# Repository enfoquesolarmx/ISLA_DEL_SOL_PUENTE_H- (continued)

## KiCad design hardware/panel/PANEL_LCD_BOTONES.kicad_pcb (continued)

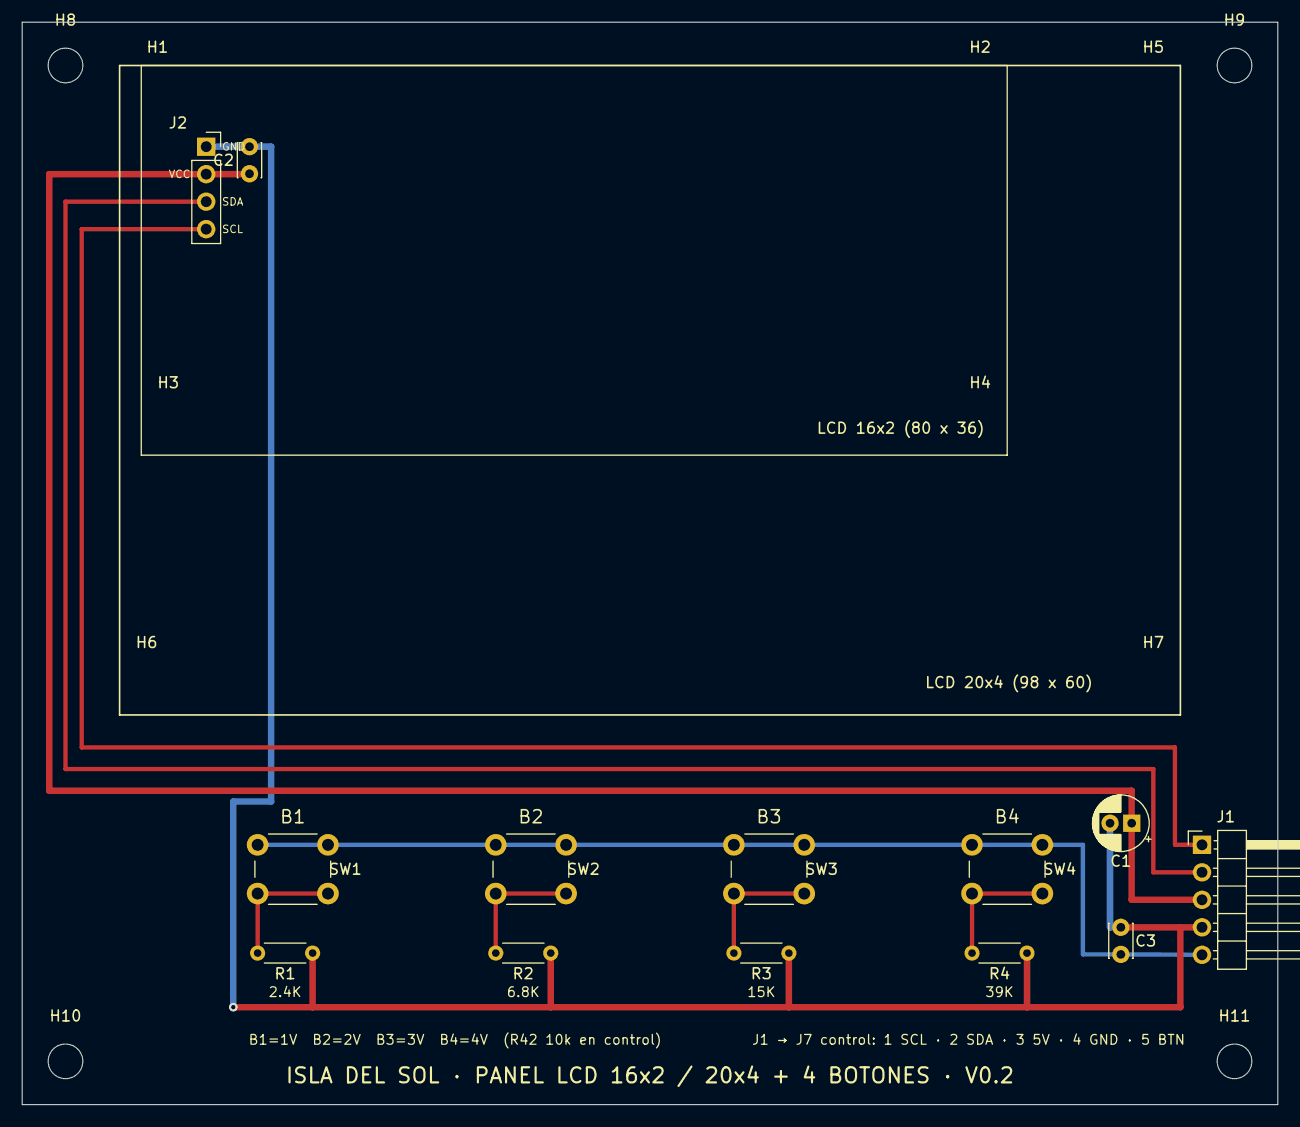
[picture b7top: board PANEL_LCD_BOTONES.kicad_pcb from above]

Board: 2 copper layers, 116.0 x 100.0 mm, 24 parts (0 on the bottom side), 9 nets.

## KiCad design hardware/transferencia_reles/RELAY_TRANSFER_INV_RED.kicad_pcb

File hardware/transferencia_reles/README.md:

# Tarjeta de transferencia de carga V0.1: 5 relés (red · inversor · cargador)

Tarjeta de potencia de 127 V que decide **de dónde se alimenta la casa**: de la **red** o del **inversor**. También conecta el **transformador a la red para cargar la batería** y hace la **unión neutro–tierra (N–PE)** cuando el inversor es la fuente principal.

Recibe tres órdenes de la tarjeta de control por un cable plano IDC de 8 hilos (J15) y no tiene microcontrolador propio. **Si se va la energía de 15 V, se suelta el cable o el microcontrolador de la tarjeta de control está en reset, todos los relés se sueltan y la casa queda en la red** (falla segura).

> ⚠️ **127 V AC en bornes, pistas y contactos de relé: pueden ser mortales.** Prototipo en desarrollo, no certificado. La decisión de diseño completa está en [DC-019](../../docs/decisiones_criticas.md) y el estudio de referencia industrial en [OutBack FX](../../docs/referencia_outback_fx.md).

*Render 3D de KiCad 9, V0.1. Arriba, la lógica de 15 V (J15, ULN2003A, Q1/Q2) y el título; abajo, los 5 relés, los bornes de 127 V y los capacitores X2/Y2. El modelo de los relés es aproximado (`3d/`).*

---

## 0. Por qué la Isla del Sol necesita esta tarjeta

La Isla del Sol es **inversor y cargador a la vez**: el mismo puente H y el **mismo transformador** sacan 127 V de la batería cuando no hay red, y la cargan desde la **red eléctrica pública** (o un generador) cuando sí hay. Ese doble papel deja tres preguntas que el puente H no puede contestar por sí solo y que esta tarjeta resuelve **con hardware**:

**1. ¿De dónde se alimenta la casa, y cómo se garantiza que nunca sea de las dos fuentes a la vez?**
Si la salida del inversor queda en paralelo con la red, aunque sea un instante:
- la red eléctrica alimenta de reversa al transformador y al puente H y lo destruye (son dos fuentes de 127 V que no están sincronizadas);
- con la red caída, el inversor **energiza la acometida**: 127 V en las líneas de la red eléctrica, donde puede haber un liniero trabajando.

Por eso la transferencia la hace un **conmutador de 2 polos y 2 tiros** (K4 + K2): el mismo contacto que conecta la casa a una fuente la desconecta de la otra. **Ni siquiera un relé soldado forma el paralelo** (análisis de falla en [DC-019](../../docs/decisiones_criticas.md)). Es el principio del equipo de transferencia de los sistemas de respaldo (NOM-001-SEDE-2012 de México, art. 702; equivalente al artículo 702 del NEC de EE. UU.).

**2. ¿Cómo se conecta el transformador a la red para cargar la batería, sin que la casa se quede sin luz?**
En modo cargador, K1 + K3 conectan el transformador al **nodo de la casa**, que sigue en la red por los contactos NC. La casa nunca se queda sin luz mientras se carga, y el candado Q1 impide que "cargar" e "invertir" se pidan al mismo tiempo.

**3. ¿Quién hace la unión neutro–tierra cuando el inversor alimenta la casa?**
Al conmutar también el neutro, el inversor se vuelve un **sistema derivado separadamente**. Necesita su propia unión N–PE (NOM-001-SEDE-2012, 250-30; NEC 250.30), pero **solo** cuando es la fuente: con la red, la unión es la de la acometida, y una segunda unión haría circular corriente por la tierra. K5 la hace de forma automática según el modo del SETUP (sección 4.1). El OutBack FX, la referencia industrial, deja esa decisión al instalador ([estudio](../../docs/referencia_outback_fx.md)).

**Y además, por diseño de la Isla del Sol:**
- **Los 127 V fuera de la tarjeta de control** ([DC-015](../../docs/decisiones_criticas.md)). El microcontrolador, el LCD y los botones solo ven 15 V y un cable plano. Toda la parte de 127 V vive aquí, con 5 mm de separación y ranuras de aislamiento.
- **Falla segura:** sin 15 V, con el cable suelto o con el microcontrolador en reset, la casa queda **en la red**. Si el inversor se apaga por cualquier causa, la casa no se queda a oscuras si hay red.
- **Reparable en la trinchera:** relés de 30 A tipo T90, ULN2003, BC547, 1N4148 y resistencias de agujero pasado. Todo se consigue en una tienda de electrónica local, se cambia con un cautín y está documentado pieza por pieza.

**Dónde se usa:**

| Instalación | Modo normal | Qué hace la tarjeta |
| --- | --- | --- |
| Casa con red inestable (respaldo) | Red | Al fallar la red pasa a inversor (modo CARGA/UPS o CASA); al volver, regresa a la red y carga la batería |
| Sitio aislado con generador | Inversor (CASA) | El generador entra como "red" para cargar la batería y alimentar la casa mientras tanto |
| Solar como fuente principal, red de respaldo | Inversor (CASA) | Usa primero el sol y la batería; la red solo para cargar o cuando la batería se agota |

## 1. Características

| Parámetro | Valor |
| --- | --- |
| Voltaje | 127 V AC / 60 Hz (fase, neutro y tierra física) |
| Corriente de diseño | **10 A RMS continuos** (1270 VA) |
| Relés | 5 × SPDT de 30 A NO / 20 A NC, familia T90. **Bobina de 15 V** (p. ej. Picker PTRH-1C-15S) o Rayex L90S de 12 V con 39 Ω (sección 12) |
| Conmuta | **Fase y neutro** (los dos polos), en transferencia y en cargador |
| Mando | ULN2003A desde 15 V; 3 canales: INV, CARG, TN |
| Candados por hardware | Q1: el inversor bloquea al cargador · Q2: la unión N–PE solo con inversor activo |
| Filtro | C_F 4.7 µF X2 del lado del transformador · CX_RED 0.1 µF X2 + CY_RED 0.1 µF Y2 del lado de la red |
| Versión | **V0.1** (2026-11). En la serigrafía: "ISLA DEL SOL · TARJETA DE TRANSFERENCIA DE CARGA · V0.1.J.G · 2026-11" |
| Placa | 158.4 × 131.1 mm, 2 capas, **1 oz**, 4 barrenos de montaje Ø4.3 mm, **4 ranuras de aislamiento** |
| Separaciones | **≥ 5 mm** de 127 V a lógica · **≥ 3 mm** entre redes de 127 V (verificado con script, secciones 9 y 10) |

## 2. Archivos

| Archivo | Qué es |
| --- | --- |
| `RELAY_TRANSFER_INV_RED.kicad_pro` | Proyecto de KiCad 9 (incluye las exclusiones del DRC: serigrafía sobre las ranuras y las 3 islas unidas por cable) |
| `RELAY_TRANSFER_INV_RED.kicad_sch` | Esquemático, en 5 bloques sobre A3 |
| `RELAY_TRANSFER_INV_RED.kicad_pcb` | Layout |
| `RELAY_TRANSFER_INV_RED.kicad_dru` | **Reglas de separación** de 5 mm y 3 mm para el DRC de KiCad (sección 10). Va en la misma carpeta que el proyecto |
| `auditoria/` | Auditoría térmica a 10 A: script, mapas e informe ([README](auditoria/README.md)) |
| `3d/` | **Modelo 3D aproximado del relé** (`Relay_SPDT_RAYEX-L90S_aprox.step`) y el script que lo genera (CadQuery). KiCad no trae el modelo oficial de esta huella; los relés lo usan con la ruta `${KIPRJMOD}/3d/...` |
| `img/` | Imágenes de este documento |

---

## 3. Cómo funciona

### 3.1 Los relés

Hay dos pares de relés iguales, uno para la **fase (L)** y otro para el **neutro (N)**, más el relé de la unión N–PE.

| Relé | Polo | Función | COM (11) | NC (12), en reposo | NO (14), energizado |
| --- | --- | --- | --- | --- | --- |
| **K4** (K_L2) | L | Transferencia | L-LOAD (casa) | **L-GRID** (red) | L-INV (transformador) |
| **K2** | N | Transferencia | N-LOAD | **N-GRID** | N-INV |
| **K1** (K_L3) | L | Cargador | L-INV | sin conectar | L-LOAD |
| **K3** | N | Cargador | N-INV | sin conectar | N-LOAD |
| **K5** (RL_TN) | N–PE | Unión neutro–tierra | N-INV | sin conectar | TIERRA |

K4 y K2 forman un **conmutador de 2 polos y 2 tiros**: la casa nunca puede tener la red y el inversor al mismo tiempo, porque es el mismo contacto el que cambia de lado.

### 3.2 Los tres canales y los modos

| Canal (salida del ULN2003) | Orden en J15 | Bobinas | LED |
| --- | --- | --- | --- |
| **INV** (AISLAR RED), salida 16 | J15-3 | K4 + K2 | D8 |
| **CARG** (TRAFO), salida 15 | J15-5 | K1 + K3 | D6 |
| **TN**, salida 14 | J15-7, **pasando por Q2** | K5 | D9 |

| Modo | INV | CARG | TN | La casa queda en | El transformador |
| --- | --- | --- | --- | --- | --- |
| **Red** (también: sin 15 V, cable suelto, microcontrolador en reset) | 0 | 0 | 0 | Red | Aislado |
| **Inversor CASA** (fuente principal) | 1 | 0 | 1 | Inversor, **con unión N–PE** (K5) | Alimenta la casa |
| **Inversor CARGA** (UPS de cargas críticas) | 1 | 0 | 0 | Inversor, **sin unión N–PE** | Alimenta las cargas |
| **Cargador** | 0 | 1 | 0 | Red | Conectado a la red por el nodo de la casa |

INV y CARG al mismo tiempo **no existe**: Q1 lo impide (sección 4).

---

## 4. Candados por hardware

*Vista previa aproximada del esquemático, dibujada desde el `.kicad_sch`. Bloques: A · entrada J15, B · candados, C · ULN2003 y LED de 15 V, D · relés, E · potencia de 127 V.*

| Candado | Cómo | Qué evita |
| --- | --- | --- |
| **Pulldowns de 10 kΩ + 10 nF** en INV_CMD, CARG_CMD y TN_OK (R7, R9, R8 y C3, C5, C4) | Con la entrada al aire, el ULN2003 queda apagado | Cable suelto, microcontrolador en reset o pin flotante → la casa queda en la red |
| **Q1** (BC547): base desde INV_CMD por R5 (10 kΩ); colector en CARG_CMD; emisor a GND | Si llega INV, Q1 jala CARG_CMD a 0 V. R11 (1 kΩ) limita la corriente si el microcontrolador manda CARG al mismo tiempo | Inversor y cargador a la vez: el transformador en paralelo con la red mientras alimenta la casa |
| **Q2** (BC547) en seguidor de emisor: colector ← TN_CMD por R13 (1 kΩ); base ← INV_CMD por R14 (10 kΩ); emisor → TN_OK | TN solo llega al ULN si INV también está activo (compuerta AND) | Una **doble unión N–PE** con la de la acometida de la red eléctrica: en modo red o cargador, K2 todavía une N-LOAD con N-GRID |
| **Entradas 4–7 del ULN2003 a GND** | Canales sin uso apagados | Ruido que encienda una salida libre |

Todas las órdenes entran por **1 kΩ en serie** (R10, R11, R13) para proteger los pines del microcontrolador si el cable se pela contra 15 V.

### ⚠️ Q2 hace dos trabajos, no uno — no lo quite

Desde **DC-023** (21 de noviembre de 2026), `TN_CMD` sale del **D13** del CRÍTICO, no del D6. D6 se liberó para `AIN0`, la entrada del comparador analógico, que está cableada en silicio y no se puede mover.

**Y D13 es el pin del LED del Nano, que el bootloader parpadea en cada arranque y en cada reset.** Sin protección, eso serían pulsos al relé K5 de unión N–PE en cada reinicio.

**Q2 es lo que lo vuelve inofensivo:**

```
  reset -> todos los pines del CRITICO en alta impedancia
        -> INV_CMD sin manejar  ->  base de Q2 sin excitar
        -> el bootloader parpadea D13 (TN_CMD)
        -> colector con senal, base sin ella  ->  TN_OK se queda BAJO
```

El orden lo garantiza: **el bootloader corre antes que la aplicación**, así que `INV_CMD` todavía no existe cuando D13 parpadea. Lo mismo vale para la programación por ICSP, donde D13 es **SCK** y conmuta a la frecuencia del programador.

> Q2 ya no es sólo el candado contra la doble unión N–PE: **también es lo que hace seguro poner `TN_CMD` en D13.** Quitarlo por «redundante» reintroduce el problema sin que se note.

**De pilón:** el LED de la tarjeta del CRÍTICO queda como **indicador de la unión N–PE**. Para una señal de seguridad eso es bueno — de un vistazo se ve si el puente está comandado.

### 4.1 Unión N–PE: automática según el modo que elige el instalador

**La unión N–PE se hace sola.** El instalador (trinchero) solo elige **una vez**, en el menú del SETUP, cómo trabaja el inversor. Desde ahí, el microcontrolador de la tarjeta de control manda o no la orden TN cada vez que pasa a inversor:

| Modo en el SETUP | Uso | Al pasar a inversor | K5 |
| --- | --- | --- | --- |
| **INVERSOR CASA** (fuente principal de la vivienda) | El inversor alimenta el tablero de la casa o del sitio aislado | El microcontrolador manda **TN = 1** junto con INV | **Cierra:** une N-INV con TIERRA (sistema derivado separadamente, NOM 250-30) |
| **INVERSOR CARGA** (UPS) | El inversor respalda cargas críticas derivadas de un circuito de la red | El microcontrolador manda **TN = 0** | Abierto: salida flotante; la unión es la de la acometida de la red eléctrica |
| Red o cargador (cualquier modo) | — | — | **Abierto siempre:** Q2 bloquea TN sin INV |

**El criterio del trinchero está en elegir bien el modo**, según cómo se va a instalar. Por eso tiene que saber de puesta a tierra: CASA solo si el equipo es la fuente principal y **no hay otra unión aguas abajo**; CARGA para un UPS que alimenta contactos o circuitos dedicados.

**Variante para un sitio aislado sin red:** se puede dejar **K5 sin poblar** y hacer una sola unión N–PE fija en el tablero. El menú se deja en CARGA, para que el microcontrolador nunca mande TN.

**Reglas:**
- **Una sola unión N–PE por sistema.** Modo CASA nunca con otra unión en el tablero; unión manual nunca con K5 poblado en modo CASA.
- **Con red conectada nunca hay doble unión:** en modo red o cargador, K2 deja el neutro de la casa en la red y Q2 bloquea a K5.
- **El modo CARGA depende del firmware.** Protecciones: de fábrica en CARGA (TN = 0); si falla el CRC de la EEPROM, regresa a CARGA; cambiar de modo solo con el inversor en espera y confirmando dos veces. **El LED D9** muestra si K5 tiene la orden.
- **Verifícalo con el multímetro** al instalar. Con el inversor alimentando y la red desconectada, mide **voltaje AC** entre N-LOAD (J1-1) y TIERRA (J9):
  - **CASA o unión manual:** ~0 V.
  - **CARGA (flotante):** un voltaje que varía. Puede marcar decenas de volts por acoplamiento capacitivo del transformador; eso es normal en una salida flotante.
  - Además, entre la fase (J2-1) y TIERRA debe haber ~127 V en CASA.

## 5. LEDs de diagnóstico (lado de 15 V)

| LED | Indica | Resistencia | Corriente |
| --- | --- | --- | --- |
| D5 | La tarjeta recibe 15 V por J15-1 | R6 4.7 kΩ | ~2.7 mA |
| D8 | Canal **INV**: bobinas de K4 + K2 con orden | R16 4.7 kΩ | ~2.6 mA |
| D6 | Canal **CARG**: K1 + K3 ("LED ON = CARG") | R15 4.7 kΩ | ~2.6 mA |
| D9 | Canal **TN**: K5 (unión N–PE) | R17 4.7 kΩ | ~2.6 mA |

**El LED dice que la bobina recibe la orden, no que el contacto cerró.** Con una bobina abierta enciende igual. Para confirmar el contacto, usa la prueba con multímetro (sección 14) o la corriente del inversor en el LCD.

**Diagnóstico del cable J15:**
- **15V apagado:** no llega energía (cable o fuente de 15 V), y todo queda en la red.
- **LED de canal apagado** aunque el LCD diga que hay orden: J15-3, -5 o -7 abierto.
- **LED encendido sin orden:** una línea pelada contra 15 V. **Revisa el cable de inmediato.**
- **Parpadeo:** GND flojo o IDC mal prensado.

---

## 6. Conectores

### 6.1 J15: cable plano desde la tarjeta de control (IDC 2×4, paso 2.54 mm)

| Pin | Señal | Pin | Señal |
| --- | --- | --- | --- |
| 1 | **15 V** | 2 | GND |
| 3 | INV (AISLAR RED) → R10 1 kΩ | 4 | GND |
| 5 | CARG (TRAFO) → R11 1 kΩ | 6 | GND |
| 7 | TN (orden de unión N–PE) → R13 1 kΩ | 8 | GND |

Cada señal va **entre dos tierras**, así el cable plano queda blindado entre hilos.

### 6.2 Potencia de 127 V

| Ref. | Tipo | Pines | Va a |
| --- | --- | --- | --- |
| **J2** | Phoenix SPT 2.5, 2 polos | 1 = L-LOAD · 2 = L-GRID | Fase: casa / red |
| **J1** | Phoenix SPT 2.5, 2 polos | 1 = N-LOAD · 2 = N-GRID | Neutro: casa / red |
| **J7** | Faston 6.3 mm (63823) | L-INV | Fase del transformador |
| **J4** | Faston 6.3 mm (63823) | N-INV | Neutro del transformador (después de L_F) |
| **J9** | Phoenix SPT 2.5, 2 polos | TIERRA / TIERRA | Tierra física: entra y sale (PE pasante) |

### 6.3 Puentes de cable (soldados, 14 AWG de 600 V)

La zona de 127 V no cabe en dos capas sin cruzar redes, así que tres redes se dividen en dos islas de cobre **unidas por cable**. Las tres son **a propósito**: el DRC y el script de revisión las marcan como islas.

| Red | Puente | Une |
| --- | --- | --- |
| L-INV | **J3 ↔ J8** | Faston J7 con el NO de K4 |
| N-INV | **J6 ↔ J5** | Faston J4 con el COM de K3 |
| N-GRID | **J12 ↔ J13** | La red con C8 (CY_RED) |

Las huellas J3, J5, J6 y J8 tienen **alivio de esfuerzo** (el cable pasa por un barreno y luego se suelda). En la serigrafía dice: *"CABLE 14 AWG · PASAR POR EL ALIVIO Y SOLDAR"*.
- El cable pasa **por encima de la zona de 127 V**, nunca sobre la lógica.
- Si cruza sobre la bobina de un relé, ponle **termocontráctil** encima del aislamiento (doble aislamiento).

### 6.4 Salidas a los transformadores de sensado

| Ref. | Pines | Para |
| --- | --- | --- |
| **J10** "FB RED" | 1 = L-GRID · 2 = N-GRID | Transformador 120 → 12 V de la red: AC_FB_GRID y PLL |
| **J11** "FB INV" | 1 = L-INV · 2 = N-INV | Transformador del inversor: AC_FB |

- Transformadores chicos de 500 mA (tipo Steren), **montados en el chasis**.
- **Fusible en línea 5×20 mm T100 mA 250 V en el cable del VIVO, pegado a J10/J11.** Usa portafusibles de 250 V, no de auto.
- Sin fusible el sensado funciona, pero el cable delgado queda sin protección.
- Conecta los dos transformadores con la **misma polaridad**: el PLL compara fases.

---

## 7. Filtro, descarga y unión N–PE

| Ref. | Valor | Entre | Para qué |
| --- | --- | --- | --- |
| **C6** (C_F) | 4.7 µF MKP **X2** 310 VAC | L-INV – N-INV | Con los ~2 mH del transformador + L_F forma el filtro LC de salida (f₀ ≈ 1.64 kHz, quita los 24 kHz). Siempre del lado del transformador, antes de los relés |
| **R18 + R19** (R_B) | 2 × 100 kΩ ½ W en serie | En paralelo con C6 | **Descarga de seguridad:** C6 baja a < 60 V en ~1 s si se desconecta el transformador. ~40 mW cada una |
| **C7** (CX_RED) | 0.1 µF MKP **X2** 275–310 VAC | L-GRID – N-GRID | EMI diferencial de la red (como el CX del OutBack FX) |
| **R20 + R21** | 2 × 470 kΩ ½ W en serie | En paralelo con C7 | Que los bornes de la red no queden cargados al desconectar. ~9 mW cada una |
| **C8** (CY_RED) | 0.1 µF **Y2** ≥ 300 VAC | N-GRID – TIERRA | EMI de alta frecuencia a tierra. Clase **Y2** porque falla abierto. Nunca X2 |
| **K5** (RL_TN) | Relé | N-INV – TIERRA | **Unión N–PE** en modo Inversor CASA (sistema derivado separadamente, NOM-001-SEDE-2012 250-30) |

**Prohibido:**
- un capacitor Y en un vivo (0.1 µF a 127 V son ~4.8 mA de fuga permanente);
- cualquier capacitor entre N-INV y PE, porque en modo Inversor CARGA "amarraría" a tierra la salida flotante.

**L_F** (inductor E65 N87) **va fuera de la tarjeta**, en el chasis, en serie con el neutro: N-TRAFO → L_F → Faston J4.

---

## 8. Layout

- **Zona de 127 V** (abajo y al centro) y **lógica de 15 V** (arriba a la izquierda), separadas por una **ranura horizontal** y con más de 5 mm de cobre a cobre.
- **4 ranuras** de 1.1–1.6 mm (en X 58, X 138 y X 172, y en Y 50.7) bajo los relés y entre zonas: alargan la distancia de fuga. El cuerpo de los relés queda encima de ellas, y el DRC lo marca como **solapamiento de courtyard**, que se excluye a propósito.
- **Zonas de 127 V con separación de 3 mm** en su configuración. La zona GND de la lógica va a 0.5 mm, y la regla de 5 mm hacia la parte de potencia la aplica `RELAY_TRANSFER_INV_RED.kicad_dru`.
- **Pistas de lógica:** **1.0 mm** para 15 V, GND, bobinas (BOB_*) y K*-A1; **0.5 mm** para las señales. Esquinas a 45°.
- **Serigrafía de advertencia:** "PELIGRO 127 V", nombres de cada borne, "BONDING TIERRA FÍSICA" en K5 y la nota de la resistencia de descarga.

### 8.1 Vistas

*Vista superior en 3D de la V0.1: título y versión en la serigrafía, arriba a la derecha (zona de 15 V). K1/K4 (fase), K2/K3 (neutro), K5 (unión N–PE); bornes Phoenix y puntos para soldar cable. El modelo de los relés es aproximado (`3d/`).*

*Cara de soldadura: título también en la serigrafía inferior, zonas de cobre de 127 V separadas, las **4 ranuras de aislamiento** (en azul) y los puntos para soldar los puentes de cable 14 AWG.*

### 8.2 Capas en el editor

*Serigrafía, contornos y pads de todas las capas.*

*F.Cu: zonas de 127 V con 3 mm entre redes; pistas de lógica de 1.0 mm (15 V, GND, bobinas) y 0.5 mm (señales).*

*B.Cu: las mismas zonas de potencia en la segunda cara (unidas por los pines THT) y el retorno de las bobinas BOB_INV / BOB_CARG por el borde izquierdo.*

## 9. Separaciones verificadas

Medidas con `pcbcheck.py`, que mide cobre contra cobre en cada capa (pads, pistas y zonas rellenas), sobre la versión final del 2026-11-11:

| Regla | Mínimo pedido | Lo más justo en la placa |
| --- | --- | --- |
| 127 V ↔ lógica de 15 V | 5 mm | **5.11 mm** (D8 contra la zona N-INV) |
| Entre redes de 127 V | 3 mm | **3.00 mm** (zona N-LOAD contra el pin NC de K3) · 3.13 mm (J10 contra N-GRID) |
| Puntos medios de los divisores (R18/R19, R20/R21) contra otra red de 127 V | 3 mm | 3.45 mm |
| Lógica contra lógica | 0.2 mm (KiCad) | 0.3 mm (CARG_CMD contra el pad R8.2) |
| Cobre contra ranura | 0.3 mm (fabricación) | 0.5 mm |

Los **contactos NC sin conectar** de K1, K3 y K5 se tratan como 127 V: en reposo tocan su COM.

## 10. Reglas de DRC

`RELAY_TRANSFER_INV_RED.kicad_dru` (cópialo junto al proyecto o pégalo en *Configuración de la placa → Reglas personalizadas*):
- **"Potencia a lógica 5 mm":** cualquier red `L-*`, `N-*`, `TIERRA`, `unconnected-(K*` o punto medio de los divisores, contra cualquier otra que no lo sea.
- **"Potencia entre redes 3 mm":** entre dos redes de potencia distintas.

El DRC final solo marca: **courtyard de los relés sobre las ranuras** (intencional) y **serigrafía encimada en conectores** (cosmético).

---

## 11. Temperatura a 10 A

Resumen de la [auditoría térmica](auditoria/README.md):

| Modo | Solo cobre | Cobre + relés |
| --- | --- | --- |
| Red → casa | +8.3 °C | +21.6 °C |
| Inversor → casa | +4.1 °C | +26.8 °C |
| Cargador (10 A de la red al transformador) | +8.3 °C | **+28.1 °C** |

- **El cobre de 1 oz no necesita refuerzo.** El calor lo ponen los relés: contactos y bobinas.
- Con 40 °C de ambiente, el pin más caliente queda en ~68 °C. El relé aguanta hasta 85 °C de ambiente.
- **El contacto es lo que decide:** un relé desgastado (15 mΩ) lleva el pin a ~110 °C. Mide la caída de cada contacto en banco.

## 12. Relés de 15 V y las huellas R1–R4, R12

| Opción | R1–R4, R12 | Bobina | Calor en la resistencia |
| --- | --- | --- | --- |
| **Elegida: relé de 15 V** (Picker PTRH-1C-15S, 375 Ω) | **Puente de alambre** | ~37 mA, 0.52 W | Ninguno |
| Respaldo: Rayex L90S de 12 V (155 Ω) | **39 Ω**, ½ W como mínimo (huella DIN0207 actual) | 77 mA, 0.93 W | 0.23 W: ~80 °C con ½ W; ~60 °C con 1 W |

- El relé de 15 V cierra con 10.25 V como máximo. Con ~14 V en la bobina (15 V menos el ULN) tiene **casi 4 V de margen**, aunque esté caliente.
- **Nunca pongas una resistencia de ¼ W:** trabajaría al 93 %, con el cuerpo a ~120 °C.
- **⚠️ Antes de fabricar, compara los pines del PTRH** contra la huella `Relay_SPDT_RAYEX-L90S`: bobina A1–A2, posición de COM, NO y NC, y diámetro de los barrenos. Los dos son de la familia T90, pero la hoja que se consultó no trae las medidas.
- **En el pedido debe decir "1C"** (SPDT): K4 y K2 usan el contacto NC.

## 13. Consumo de 15 V y del ULN2003

| Modo | Bobinas encendidas | Corriente de 15 V (relés de 15 V) | Con L90S + 39 Ω |
| --- | --- | --- | --- |
| Red | 0 | ~3 mA (LED de 15 V) | ~3 mA |
| Inversor CASA | K4, K2, K5 | **~120 mA** | ~240 mA |
| Cargador | K1, K3 | ~80 mA | ~160 mA |

- **Fuente de 15 V: 0.3 A como mínimo, 0.5 A recomendada.** Si la fuente se cae de voltaje, los relés pueden vibrar justo en la transferencia.
- **ULN2003:** como máximo 2 bobinas por canal; disipa < 0.2 W. Su COM (pin 9) va a 15 V, así que sus diodos internos también sirven de rueda libre. Además hay **1N4148** externos (D1–D4, D7).

---

## 14. Ensamble y validación

**Orden de ensamble:**
1. Lógica: resistencias, LEDs, Q1/Q2, ULN2003 (en zócalo), C1/C2, J15.
2. **Prueba sin relés:** 15 V por J15, y verifica con un multímetro:
   - D5 enciende con 15 V;
   - INV → D8; CARG → D6; TN solo junto con INV → D9;
   - INV + CARG juntos → solo D8 (Q1);
   - TN sin INV → nada (Q2).
3. Puentes R1–R4 y R12 (relé de 15 V) o resistencias de 39 Ω (L90S de 12 V).
4. Relés, capacitores de 127 V, bornes y fastons.
5. **Puentes de cable 14 AWG** J3↔J8, J6↔J5, J12↔J13, pasados por el alivio y soldados.

**Antes de conectar 127 V, con el multímetro:**
- No hay continuidad entre L-GRID y N-GRID, L-INV y N-INV, ni entre cualquier borne de 127 V y J15.
- Sin 15 V: L-GRID ↔ L-LOAD y N-GRID ↔ N-LOAD tienen continuidad (contactos NC); L-INV ↔ L-LOAD está abierto.
- Con INV activo: L-INV ↔ L-LOAD tiene continuidad; L-GRID ↔ L-LOAD está abierto.
- Con INV + TN: N-INV ↔ TIERRA tiene continuidad (K5).

**Con carga (10 A resistivos):**
- Caída en cada contacto cerrado: **< 50 mV** ✅ · 50–150 mV 👍 · > 150 mV ⚠️ cambia el relé.
- Después de 1 hora en modo cargador, ningún pin a más de **+35 °C** sobre el ambiente.
- Prueba periódica de "relé soldado": con orden INV, **0 V entre L-GRID y L-LOAD**.

---

## 15. Lista de materiales

| Cant. | Ref. | Valor | Huella / nota |
| --- | --- | --- | --- |
| 4 + 1 | K1–K4 + K5 | Relé SPDT 30 A, **bobina 15 V** (Picker PTRH-1C-15S) · respaldo: Rayex L90S 12 V. K5 puede quedar sin poblar en un sitio aislado con unión fija (sección 4.1) | `Relay_SPDT_RAYEX-L90S` |
| 5 | R1–R4, R12 | **Puente** (relé de 15 V) · 39 Ω ½ W (L90S de 12 V; así está en los archivos) | DIN0207, 10.16 mm |
| 1 | U1 | ULN2003A | DIP-16, con zócalo |
| 2 | Q1, Q2 | BC547 | TO-92 |
| 5 | D1–D4, D7 | 1N4148 | DO-35 |
| 4 | D5, D6, D8, D9 | LED verde 3 mm | |
| 4 | R6, R15, R16, R17 | 4.7 kΩ ¼ W | DIN0204 |
| 3 | R10, R11, R13 | 1 kΩ ¼ W | DIN0204 |
| 5 | R5, R7, R8, R9, R14 | 10 kΩ ¼ W | DIN0204 |
| 2 | R18, R19 | 100 kΩ ½ W | DIN0207 |
| 2 | R20, R21 | 470 kΩ ½ W | DIN0207 |
| 1 | C6 | 4.7 µF MKP **X2** 310 VAC | MKS4, paso 27.5 mm |
| 1 | C7 | 0.1 µF MKP **X2** 275–310 VAC | FKS3, paso 15 mm |
| 1 | C8 | 0.1 µF **Y2** ≥ 300 VAC | MKS4, paso 22.5 mm |
| 3 | C3, C4, C5 | 10 nF cerámico | |
| 1 | C1 | 100 nF cerámico | |
| 1 | C2 | 100 µF electrolítico, ≥ 25 V | Radial, 10 mm |
| 1 | J15 | IDC 2×4 macho, paso 2.54 mm | |
| 5 | J1, J2, J9, J10, J11 | Phoenix SPT 2.5 de 2 polos, paso 5.0 mm | |
| 2 | J4, J7 | Faston macho 6.3 mm para PCB (63823) | |
| 6 | J3, J5, J6, J8, J12, J13 | Puntos para soldar cable 14 AWG de 600 V | Con alivio: J3, J5, J6, J8 |
| 2 | — | Portafusibles en línea de 250 V + fusible 5×20 mm T100 mA | En el vivo de J10 y de J11 |

**Fuera de la tarjeta** (DC-019, punto 8): fusible lento de 10–12 A en el camino del cargador, breaker de 20 A hacia la casa, MOV 14D241K en la salida a la casa, y L_F en el neutro del transformador.

---

## 16. Diferencias con DC-019 y pendientes

La tarjeta construida **no coincide** en estos puntos con lo escrito en [DC-019](../../docs/decisiones_criticas.md). Hay que decidir cada uno y actualizar el que corresponda: la tarjeta o el documento.

| # | DC-019 dice | La tarjeta tiene | Impacto |
| --- | --- | --- | --- |
| 1 | **SW_TN**: selector DPDT en la tarjeta de relés. Polo A en serie con la bobina de RL_TN; polo B lleva **MODO_TN** a J15-8 | **No hay SW_TN**, y J15-8 es GND | ✅ **Decidido (2026-11-11): sin selector físico.** La unión es **automática según el modo del SETUP** (CASA → TN = 1; CARGA/UPS → TN = 0), la manda el microcontrolador por J15-7 y Q2 la condiciona a INV (sección 4.1). DC-019 actualizado (puntos 9 y 10) |
| 2 | Un LED **por relé**, 2.2 kΩ (~6 mA), azules para INV y ámbar para CARG | Un LED **por canal**, todos verdes y **todos con 4.7 kΩ** (~2.6 mA) | ✅ **Resuelto en la tarjeta (2026-11-11):** los cuatro LED brillan igual. DC-019 actualizado (punto 11) |
| 3 | Relés L90S de 12 V + **39 Ω ½ W** (punto 7) | Decisión del 2026-11-11: **relé de 15 V + puente** | ✅ DC-019 actualizado (punto 7) |
| 4 | El transformador va hacia K_L3/K3 por **puentes faston con seguro** (seccionador de servicio del cargador) | Fastons J7/J4 directos; los puentes J3↔J8 y J6↔J5 son **cable soldado** y solo sirven al layout | Decidir si el seccionador de servicio va fuera de la tarjeta |
| 5 | Rueda libre con los diodos internos del ULN2003 | Diodos internos **y** 1N4148 externos | Ninguno: redundancia |

**Otros pendientes:**
- Comparar los pines del PTRH-1C-15S contra la huella (sección 12).
- ✅ Serigrafía: "TIERRA GND" cambiado a **"TIERRA FÍSICA"**. Las cotas de medición están en la capa Dwgs.User, que no sale en los Gerber.
- F_CARG y MOV 14D241K: confirmar que van fuera de la tarjeta.
- La nota **"PENDIENTES DC-019 (no dibujados aún)"** del bloque E del esquemático está desactualizada: R_B, CX_RED, CY_RED y el capacitor de 100 nF en U1.9 (C1) ya están dibujados. Solo quedan F_CARG y el MOV (SW_TN se eliminó).

---

## 17. Bitácora (tres días de revisión, hasta el 2026-11-11)

| Etapa | Cambio |
| --- | --- |
| Día 1 | Esquemático reorganizado en 5 bloques sobre A3. Revisión de candados: Q1 estaba volteado; Q2 tenía colector y emisor con la misma etiqueta (en corto); TIERRA en el NC de K5 (doble unión); J11.2 sin conectar |
| Día 2 | Se agregan R18/R19 (descarga de C6), C7 + R20/R21 (CX_RED), C8 Y2 (CY_RED) y J10/J11 (sensado). C8 corregido de X2 a **Y2**, y de disco cerámico a MKP |
| Día 2 | Ranuras de aislamiento; puentes de cable soldados con alivio en lugar de fastons |
| Día 3 | Pista L-RD entre los pads de L-GRID de J10 (1.5 mm) → R20/R21 reacomodadas (≥ 3.45 mm). Zonas de 127 V a 3 mm. Choque de N-LOAD con el NC de K3 corregido |
| Día 3 | Zona GND puesta por error a 5 mm (se vació la lógica) → regresa a 0.5 mm, y los 5 mm se aplican con reglas personalizadas (`.kicad_dru`) |
| Día 3 | Pulido de la lógica: anchos en dos clases, 11 esquinas a 45°. BOB_INV y BOB_CARG paralelas a 0.2 mm → 0.7 mm |
| Día 3 | R16 de 2.2 kΩ → 4.7 kΩ (LEDs iguales). Serigrafía "TIERRA GND" → "TIERRA FÍSICA" |
| Día 3 | SW_TN eliminado: unión N–PE automática según el modo del SETUP (CASA / UPS), por el microcontrolador y Q2 |
| Día 3 | Auditoría térmica a 10 A. Las 39 Ω de ¼ W trabajaban al 93 % → ½ W → **relés de 15 V sin resistencia** |

## 18. Referencias

1. [DC-019: transferencia red / inversor / cargador](../../docs/decisiones_criticas.md)
2. [Estudio de referencia: OutBack FX](../../docs/referencia_outback_fx.md)
3. Rayex/Recoy, *L90 series power relay*. https://www.rcscomponents.kiev.ua/datasheets/L90RECOY.pdf
4. Picker Components, *PTRH 30 Amp Power PCB Relay*. https://dtsheet.com/doc/1306933/30-amp-power-pcb-relay-ptrh-ot
5. NOM-001-SEDE-2012, artículos 250-24 y 250-30 (unión N–PE, sistemas derivados separadamente).
6. IEC 60384-14 (capacitores clase X e Y).
7. IPC-2221 (corriente y calentamiento de pistas).

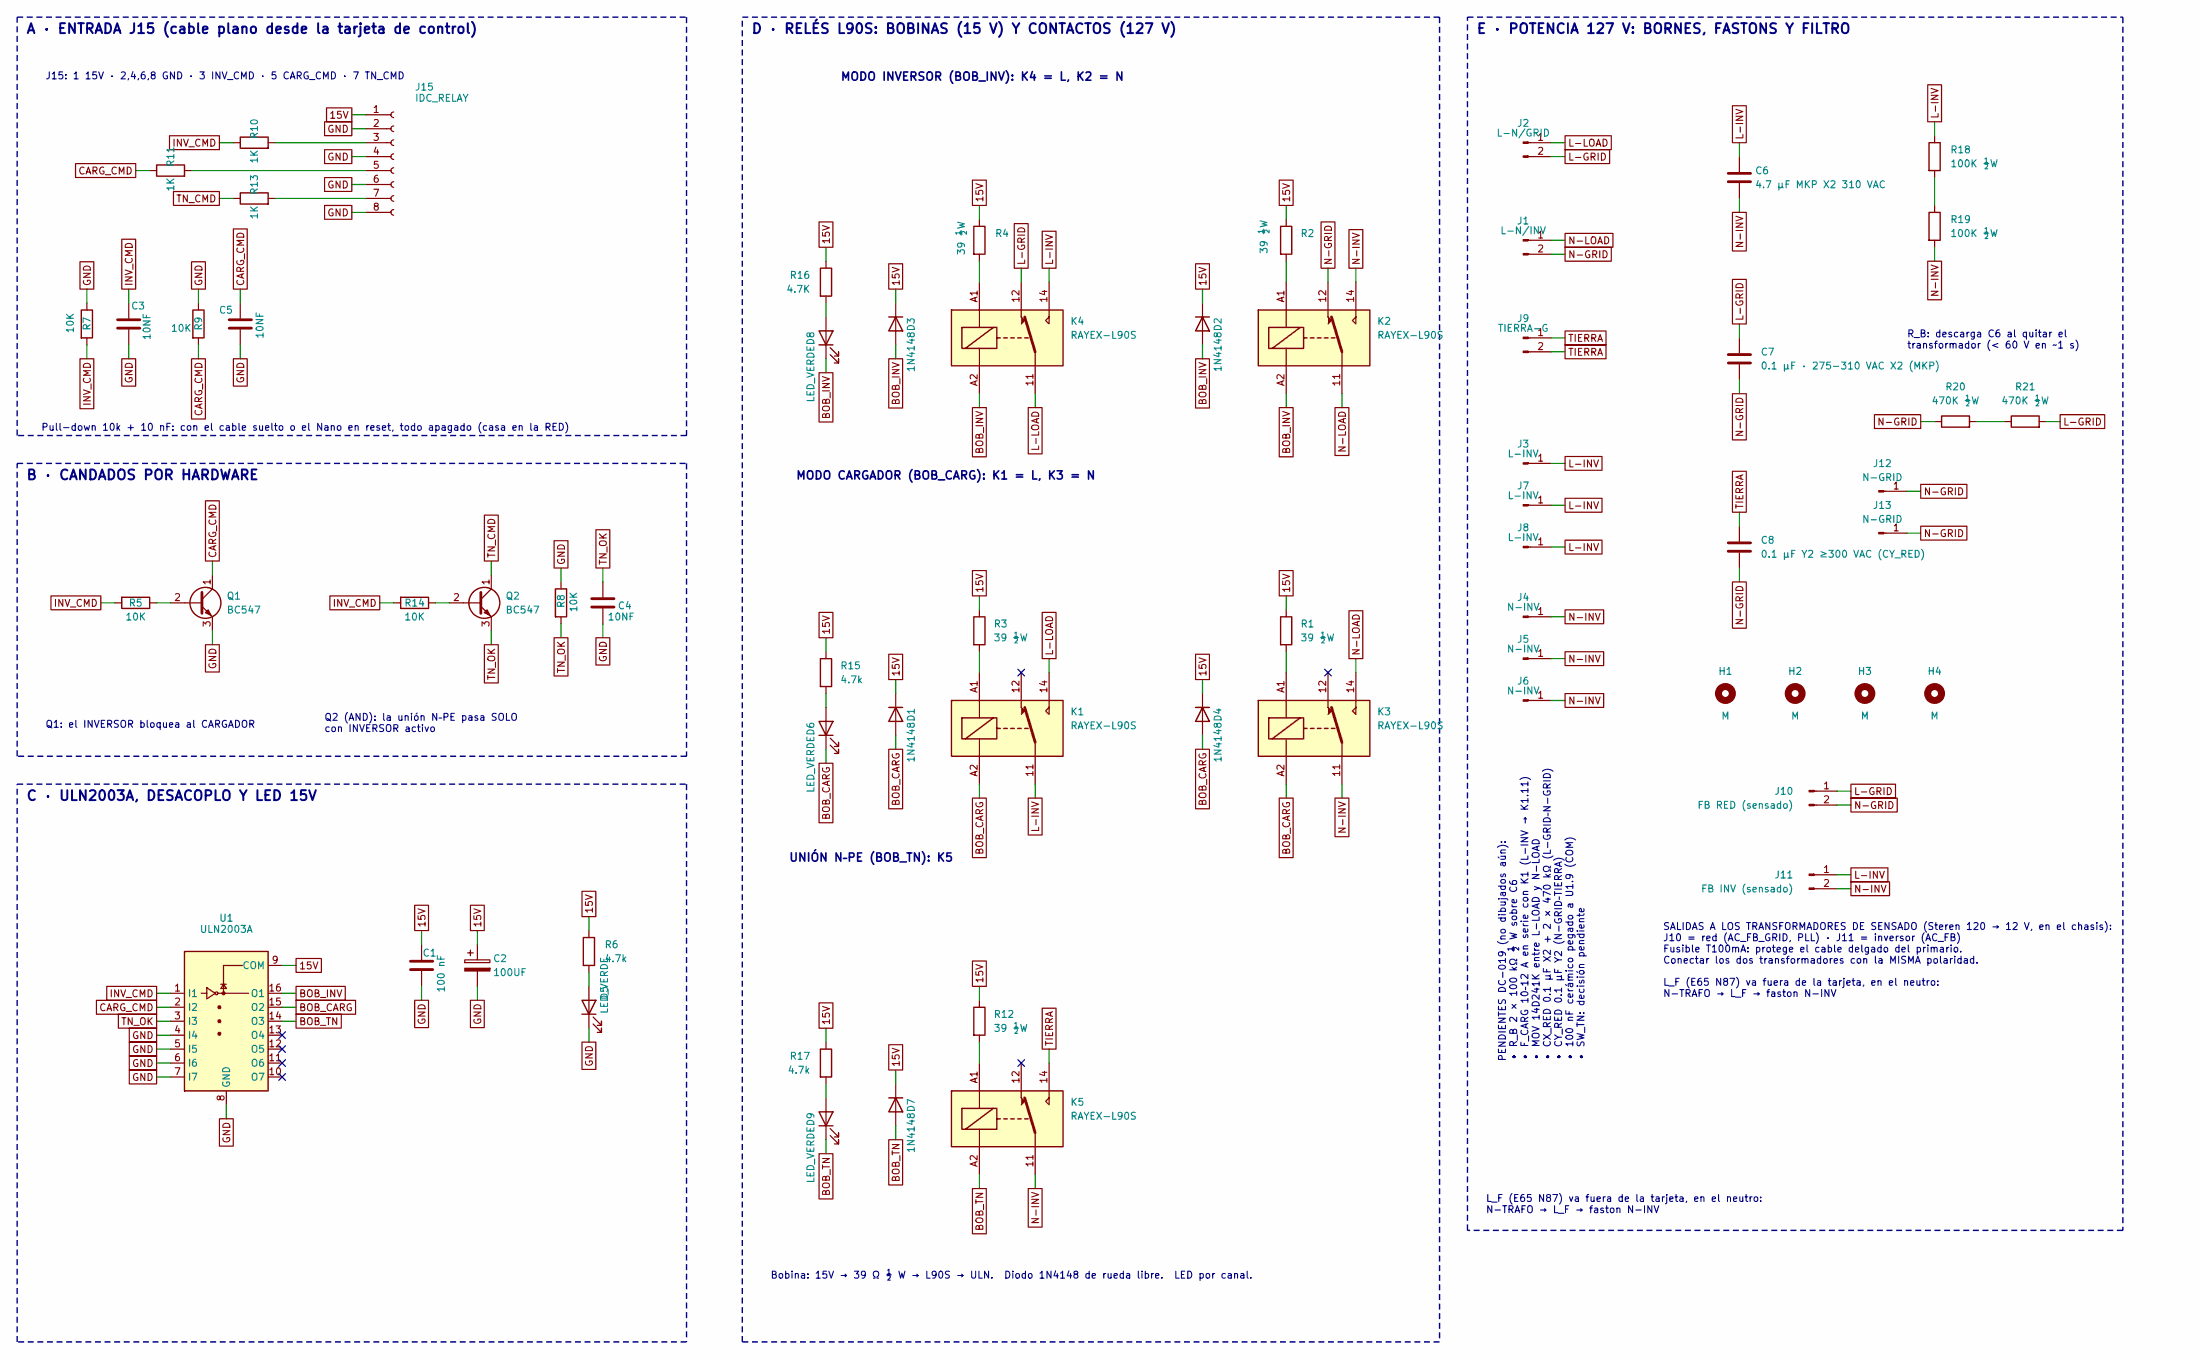
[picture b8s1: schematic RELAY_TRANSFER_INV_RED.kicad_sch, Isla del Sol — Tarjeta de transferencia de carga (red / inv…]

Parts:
C1: 100 nF; C_Disc_D3.0mm_W1.6mm_P2.50mm
C2: 100UF; CP_Radial_D10.0mm_P3.50mm
C3, C4, C5: 10NF; C_Disc_D3.0mm_W1.6mm_P2.50mm
C6: 4.7 µF MKP X2 310 VAC; C_Rect_L31.5mm_W20.0mm_P27.50mm_MKS4
C7: 0.1 µF · 275-310 VAC X2 (MKP); C_Rect_L18.0mm_W6.0mm_P15.00mm_FKS3_FKP3
C8: 0.1 µF Y2 ≥300 VAC (CY_RED); C_Rect_L26.5mm_W8.5mm_P22.50mm_MKS4
D1, D2, D3, D4, D7: 1N4148; D_DO-35_SOD27_P7.62mm_Horizontal
D5, D6, D8, D9: LED_VERDE; LED_D3.0mm
H1, H2, H3, H4: M; MountingHole_4.3mm_M4
J1: L-N/INV; PhoenixContact_SPT_2.5_2-V-5.0-EX_1x02_P5.0mm_Vertical
J2: L-N/GRID; PhoenixContact_SPT_2.5_2-V-5.0-EX_1x02_P5.0mm_Vertical
J3, J8: L-INV; SolderWire-2.5sqmm_1x01_D2.4mm_OD3.6mm_Relief
J4: N-INV; Faston 63823
J5, J6: N-INV; SolderWire-2.5sqmm_1x01_D2.4mm_OD3.6mm_Relief
J7: L-INV; Faston 63823
J9: TIERRA-G; PhoenixContact_SPT_2.5_2-V-5.0-EX_1x02_P5.0mm_Vertical
J10: FB RED (sensado); PhoenixContact_SPT_2.5_2-V-5.0-EX_1x02_P5.0mm_Vertical
J11: FB INV (sensado); PhoenixContact_SPT_2.5_2-V-5.0-EX_1x02_P5.0mm_Vertical
J12, J13: N-GRID; SolderWire-2.5sqmm_1x01_D2.4mm_OD3.6mm
J15: IDC_RELAY; IDC-Header_2x04_P2.54mm_Vertical
K1, K2, K3, K4, K5: RAYEX-L90S; Relay_SPDT_RAYEX-L90S
Q1, Q2: BC547; TO-92_Inline_Wide
R1, R2, R3, R4, R12: 39 ½W; R_Axial_DIN0207_L6.3mm_D2.5mm_P10.16mm_Horizontal
R5, R7, R8, R9, R14: 10K; R_Axial_DIN0204_L3.6mm_D1.6mm_P5.08mm_Horizontal
R6, R15, R17: 4.7k; R_Axial_DIN0204_L3.6mm_D1.6mm_P5.08mm_Horizontal
R10, R11, R13: 1K; R_Axial_DIN0204_L3.6mm_D1.6mm_P5.08mm_Horizontal
R16: 4.7K; R_Axial_DIN0204_L3.6mm_D1.6mm_P5.08mm_Horizontal
R18, R19: 100K ½W; R_Axial_DIN0207_L6.3mm_D2.5mm_P10.16mm_Horizontal
R20, R21: 470K ½W; R_Axial_DIN0207_L6.3mm_D2.5mm_P10.16mm_Horizontal
U1: ULN2003A; DIP-16_W7.62mm

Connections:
15V: C1.2, C2.1, D1.1 (K), D2.1 (K), D3.1 (K), D4.1 (K), D7.1 (K), J15.1, R1.1, R2.1, R3.1, R4.1, R6.1, R12.1, R15.1, R16.1, R17.1, U1.9 (COM)
BOB_CARG: D1.2 (A), D4.2 (A), D6.1 (K), K1.A2, K3.A2, U1.15 (O2)
BOB_INV: D2.2 (A), D3.2 (A), D8.1 (K), K2.A2, K4.A2, U1.16 (O1)
BOB_TN: D7.2 (A), D9.1 (K), K5.A2, U1.14 (O3)
CARG_CMD: C5.2, Q1.1 (C), R9.2, R11.1, U1.2 (I2)
GND: C1.1, C2.2, C3.1, C4.1, C5.1, D5.1 (K), J15.2, J15.4, J15.6, J15.8, Q1.3 (E), R7.1, R8.1, R9.1, U1.4 (I4), U1.5 (I5), U1.6 (I6), U1.7 (I7), U1.8 (GND)
INV_CMD: C3.2, R5.2, R7.2, R10.1, R14.2, U1.1 (I1)
L-GRID: C7.1, J2.2, J10.1, K4.12, R21.2
L-INV: C6.1, J3.1, J7.1, J8.1, J11.1, K1.11, K4.14, R18.1
L-LOAD: J2.1, K1.14, K4.11
N-GRID: C7.2, C8.2, J1.2, J10.2, J12.1, J13.1, K2.12, R20.1
N-INV: C6.2, J4.1, J5.1, J6.1, J11.2, K2.14, K3.11, K5.11, R19.2
N-LOAD: J1.1, K2.11, K3.14
unnamed: D5.2 (A), R6.2
unnamed: D6.2 (A), R15.2
unnamed: D8.2 (A), R16.2
unnamed: D9.2 (A), R17.2
unnamed: J15.3, R10.2
unnamed: J15.5, R11.2
unnamed: J15.7, R13.2
unnamed: K1.A1, R3.2
unnamed: K2.A1, R2.2
unnamed: K3.A1, R1.2
unnamed: K4.A1, R4.2
unnamed: K5.A1, R12.2
unnamed: Q1.2 (B), R5.1
unnamed: Q2.2 (B), R14.1
unnamed: R18.2, R19.1
unnamed: R20.2, R21.1
TIERRA: C8.1, J9.1, J9.2, K5.14
TN_CMD: Q2.1 (C), R13.1
TN_OK: C4.2, Q2.3 (E), R8.2, U1.3 (I3)

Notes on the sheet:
B · CANDADOS POR HARDWARE
E · POTENCIA 127 V: BORNES, FASTONS Y FILTRO
Q1: el INVERSOR bloquea al CARGADOR
Pull-down 10k + 10 nF: con el cable suelto o el Nano en reset, todo apagado (casa en la RED)
J15: 1 15V · 2,4,6,8 GND · 3 INV_CMD · 5 CARG_CMD · 7 TN_CMD
Bobina: 15V → 39 Ω ½ W → L90S → ULN. Diodo 1N4148 de rueda libre. LED por canal.
R_B: descarga C6 al quitar el transformador (< 60 V en ~1 s)
D · RELÉS L90S: BOBINAS (15 V) Y CONTACTOS (127 V)
UNIÓN N–PE (BOB_TN): K5
Q2 (AND): la unión N–PE pasa SOLO con INVERSOR activo
C · ULN2003A, DESACOPLO Y LED 15V
SALIDAS A LOS TRANSFORMADORES DE SENSADO (Steren 120 → 12 V, en el chasis): J10 = red (AC_FB_GRID, PLL) · J11 = inversor (AC_FB) Fusible T100mA: protege el cable delgado del primario. Conectar los dos transformadores con la MISMA polaridad.
MODO CARGADOR (BOB_CARG): K1 = L, K3 = N
MODO INVERSOR (BOB_INV): K4 = L, K2 = N
L_F (E65 N87) va fuera de la tarjeta, en el neutro: N-TRAFO → L_F → faston N-INV
PENDIENTES DC-019 (no dibujados aún): • R_B 2 × 100 kΩ ½ W sobre C6 • F_CARG 10–12 A en serie con K1 (L-INV → K1.11) • MOV 14D241K entre L-LOAD y N-LOAD • CX_RED 0.1 µF X2 + 2 × 470 kΩ (L-GRID–N-GRID) • CY_RED 0.1 µF Y2 (N-GRID–TIERRA) • 100 nF cerámico pegado a U1.9 (COM) • SW_TN: decisión pendien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
A · ENTRADA J15 (cable plano desde la tarjeta de control)

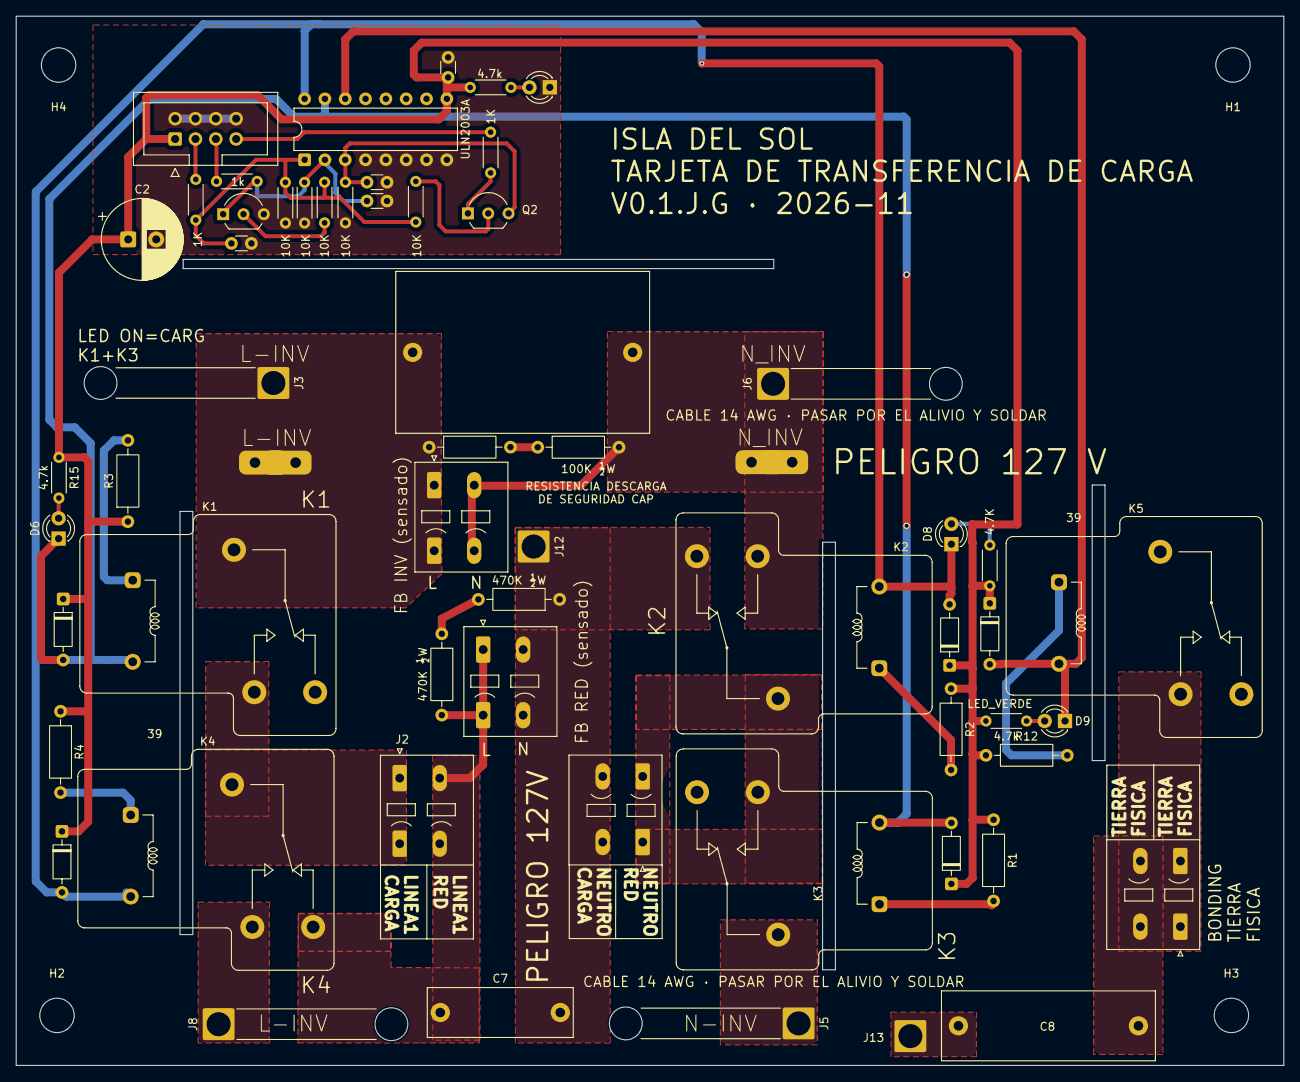
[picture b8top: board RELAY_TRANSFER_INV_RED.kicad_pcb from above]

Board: 2 copper layers, 158.4 x 131.1 mm, 64 parts (0 on the bottom side), 32 nets.

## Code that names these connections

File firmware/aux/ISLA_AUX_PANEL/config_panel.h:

/*
 * =============================================================================
 *  config_panel.h  -  Isla del Sol, micro AUX (A2): panel LCD 16x2 + botonera
 * -----------------------------------------------------------------------------
 *  AQUÍ SE ESCOGE LA PANTALLA (filosofía UNIX: una sola perilla, en el script).
 *
 *    LCD_TIPO = 1  ->  AIP31068  (LCD I2C "nativo", dirección 0x3E).
 *                      Es el que trae SimulIDE 1.1 y el de los Grove LCD.
 *    LCD_TIPO = 0  ->  PCF8574 + HD44780 (el 16x2 "normal" con mochila I2C
 *                      azul que venden en todas las tiendas, 0x27 o 0x3F).
 *
 *  Cambia el número, compila y sube. Nada más cambia.
 *
 *  BUS DE LA PANTALLA (hardware/control, mapa de pines del AUX)
 *    D4 = SDA_LCD, D5 = SCL_LCD  ->  I2C por software, SEPARADO del enlace
 *    con el CRÍTICO (A4/A5). Así una pantalla trabada o un cable largo del
 *    panel nunca tumba el enlace de control.
 *    Pull-ups: el Nano pone las internas (~35 kΩ), pero con cable de panel o
 *    en SimulIDE pon 4.7 kΩ a 5 V en D4 y D5.
 *
 *  Licencia: MIT (ver LICENSE.md del repositorio).
 * =============================================================================
 */
#pragma once
#include <stdint.h>

// ======================== LA PERILLA =========================================
#define LCD_TIPO 1          // 1 = AIP31068 (SimulIDE / Grove), 0 = PCF8574 16x2

// ======================== DIRECCIONES (7 bits) ===============================
constexpr uint8_t LCD_DIR_AIP31068 = 0x3E;
constexpr uint8_t LCD_DIR_PCF8574  = 0x27;  // si tu mochila es PCF8574A: 0x3F

// ======================== PINES ==============================================
constexpr uint8_t PIN_SDA_LCD  = 4;
constexpr uint8_t PIN_SCL_LCD  = 5;
constexpr uint8_t PIN_BOTONES  = A7;        // escalera de resistencias (panel §3)
constexpr uint8_t PIN_AUX_KILL = 7;         // AUX_KILL: HIGH = no matar (mapa de pines)
constexpr uint8_t PIN_CS_CAN   = 10;        // D10 debe ser OUTPUT (SPI maestro)

// ======================== I2C POR SOFTWARE ===================================
// Medio periodo en µs. 5 µs + lo que tarda digitalWrite ≈ 50–70 kHz.
constexpr uint8_t I2C_SW_MEDIO_PERIODO_US = 5;
// Tiempo máximo esperando que el esclavo suelte SCL (clock stretching).
constexpr uint16_t I2C_SW_ESPERA_SCL_US = 1000;
